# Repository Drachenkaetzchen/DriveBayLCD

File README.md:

This is a controller board for the DOGM LCD which can be controlled via USB. It is designed to fit into the 5 1/4" drive bay of your computer. It supports 6 LEDs and 6 Switches/Buttons.

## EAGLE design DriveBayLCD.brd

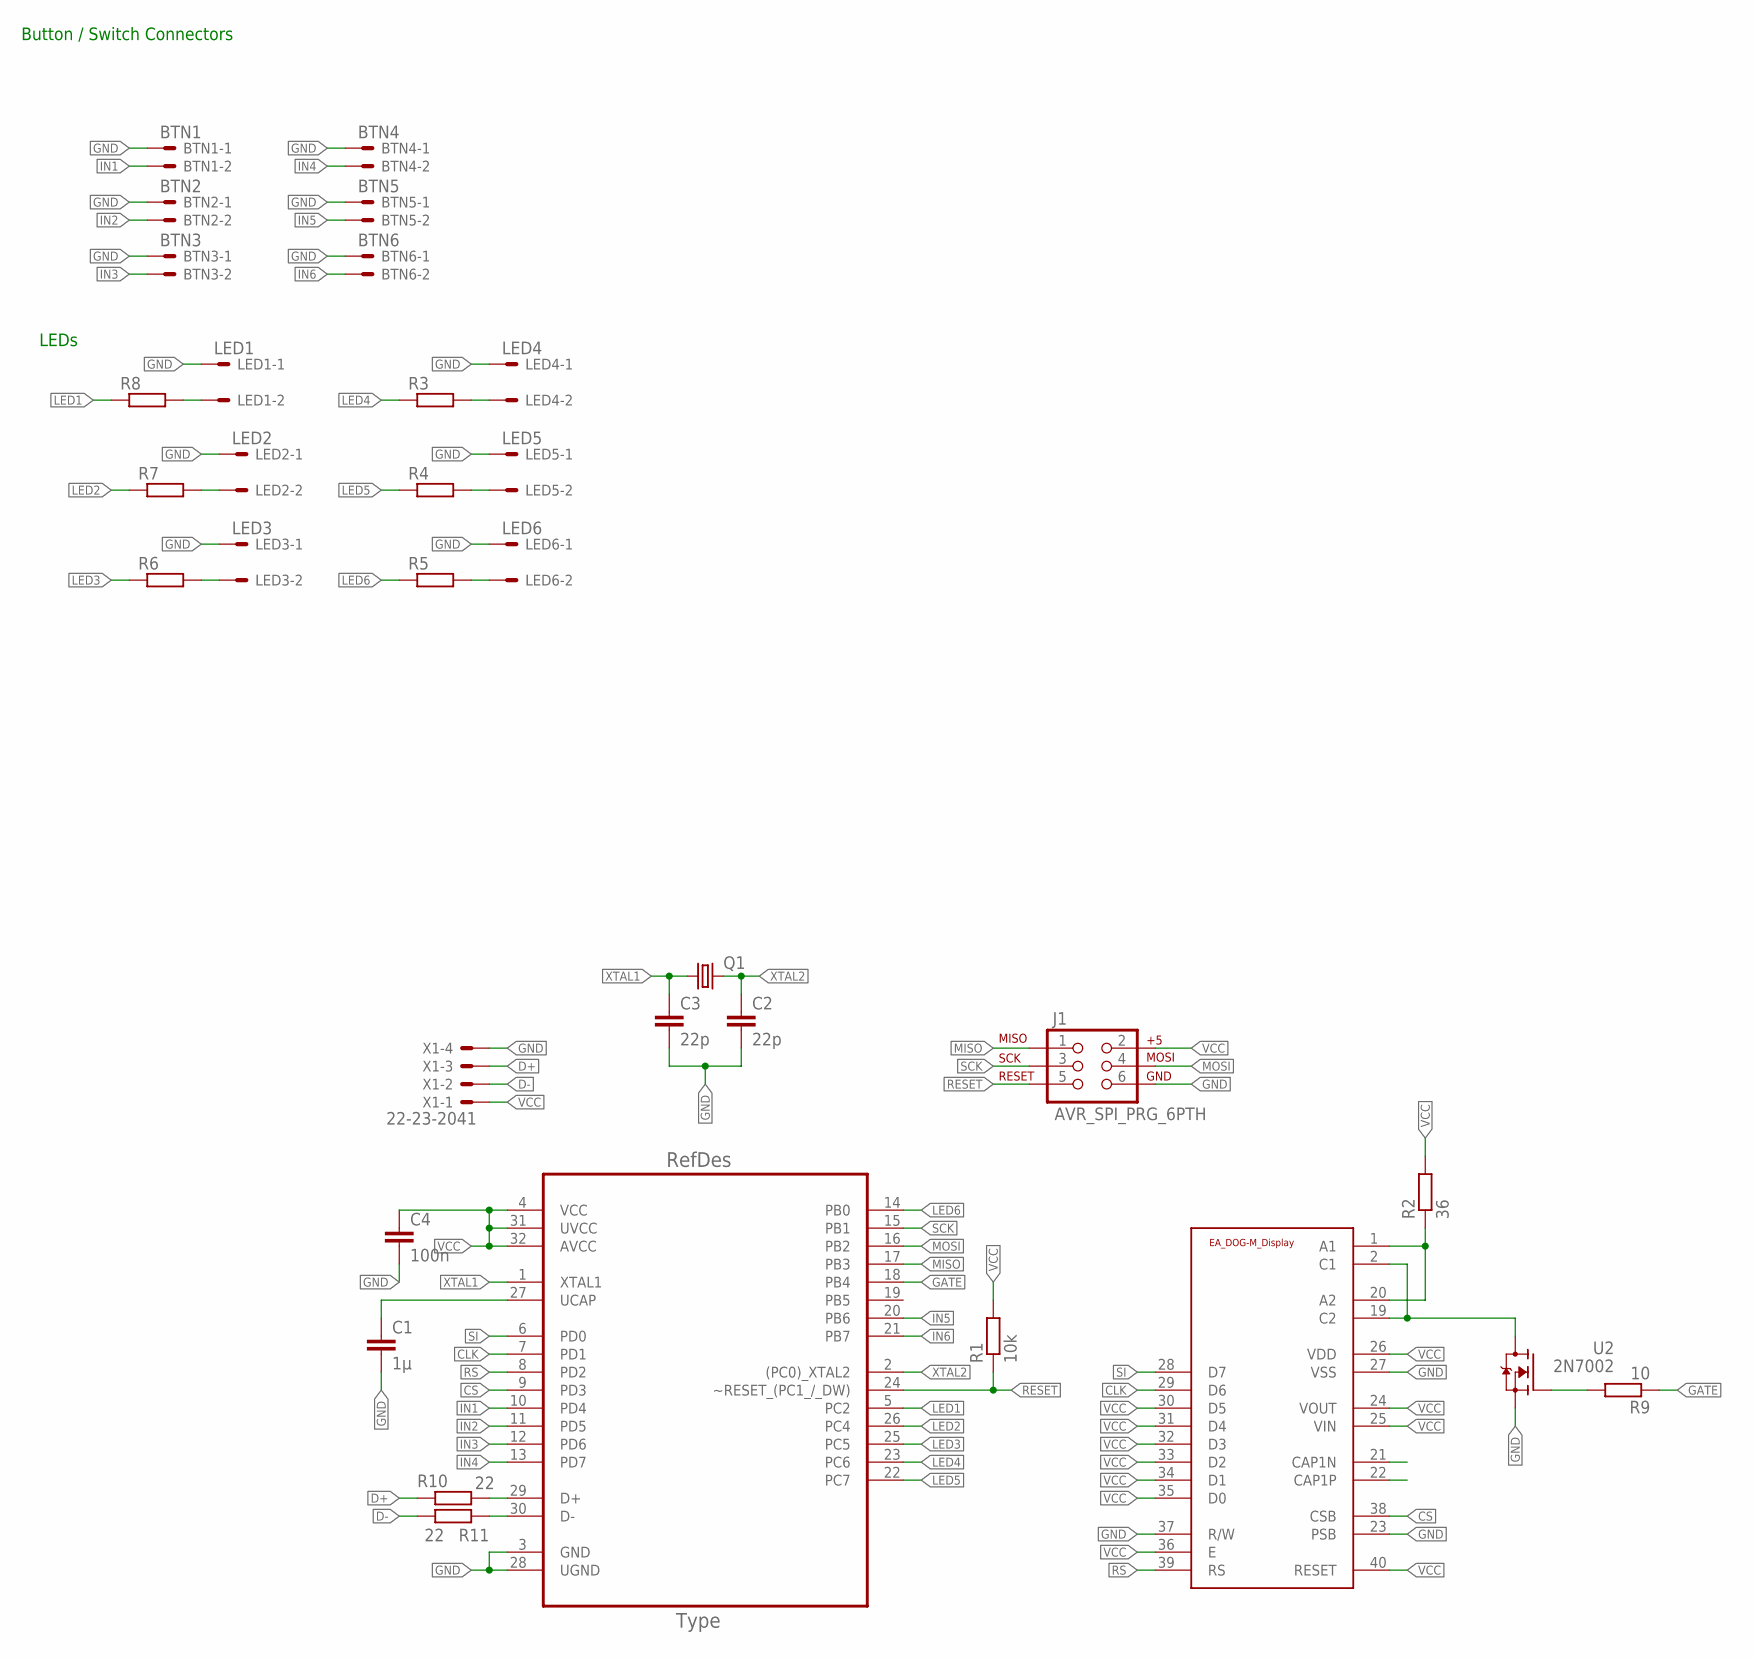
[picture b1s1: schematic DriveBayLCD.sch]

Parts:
BTN1: BTN1; 22-23-2021
BTN2: BTN2; 22-23-2021
BTN3: BTN3; 22-23-2021
BTN4: BTN4; 22-23-2021
BTN5: BTN5; 22-23-2021
BTN6: BTN6; 22-23-2021
C1: 1µ; C0805
C2, C3: 22p; C0805
C4: 100n; C0805
J1: AVR_SPI_PRG_6PTH; 2X3
LED1: LED1; 22-23-2021
LED2: LED2; 22-23-2021
LED3: LED3; 22-23-2021
LED4: LED4; 22-23-2021
LED5: LED5; 22-23-2021
LED6: LED6; 22-23-2021
Q1: CRYSTALHC49S; HC49/S
R1: 10k; R0805
R2: 36; R0805
R3, R4, R5, R6, R7, R8: R-EU_R0805; R0805
R9: 10; R0805
R10, R11: 22; R0805
U1: ATMEGA32U2-AU; QFP80P900X900X120-32N
U2: 2N7002; SOT23-3-ROTATED
U$1: EA_DOG-M_DISPLAY; E_DOG-M_DISPLAY
X1: 22-23-2041

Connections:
CLK: U1.7 (PD1), U$1.29 (D6)
CS: U1.9 (PD3), U$1.38 (CSB)
D+: R10.2, X1.3
D-: R11.2, X1.2
GATE: R9.1, U1.18 (PB4)
GND: BTN1.1, BTN2.1, BTN3.1, BTN4.1, BTN5.1, BTN6.1, C1.2, C2.2, C3.2, C4.2, J1.6, LED1.1, LED2.1, LED3.1, LED4.1, LED5.1, LED6.1, U1.3 (GND), U1.28 (UGND), U2.2 (S), U$1.23 (PSB), U$1.27 (VSS), U$1.37 (R/W), X1.4
IN1: BTN1.2, U1.10 (PD4)
IN2: BTN2.2, U1.11 (PD5)
IN3: BTN3.2, U1.12 (PD6)
IN4: BTN4.2, U1.13 (PD7)
IN5: BTN5.2, U1.20 (PB6)
IN6: BTN6.2, U1.21 (PB7)
LED1: R8.1, U1.5 (PC2)
LED2: R7.1, U1.26 (PC4)
LED3: R6.1, U1.25 (PC5)
LED4: R3.1, U1.23 (PC6)
LED5: R4.1, U1.22 (PC7)
LED6: R5.1, U1.14 (PB0)
MISO: J1.1, U1.17 (PB3)
MOSI: J1.4, U1.16 (PB2)
unnamed: LED1.2, R8.2
unnamed: LED2.2, R7.2
unnamed: LED3.2, R6.2
unnamed: LED6.2, R5.2
unnamed: C1.1, U1.27 (UCAP)
unnamed: LED5.2, R4.2
unnamed: LED4.2, R3.2
unnamed: R2.1, U$1.1 (A1), U$1.20 (A2)
unnamed: R9.2, U2.1 (G)
unnamed: R10.1, U1.29 (D+)
unnamed: R11.1, U1.30 (D-)
RESET: J1.5, R1.1, U1.24 (~RESET_(PC1_/_DW))
RS: U1.8 (PD2), U$1.39 (RS)
SCK: J1.3, U1.15 (PB1)
SI: U1.6 (PD0), U$1.28 (D7)
V$1: U2.3 (D), U$1.2 (C1), U$1.19 (C2)
VCC: C4.1, J1.2, R1.2, R2.2, U1.4 (VCC), U1.31 (UVCC), U1.32 (AVCC), U$1.24 (VOUT), U$1.25 (VIN), U$1.26 (VDD), U$1.30 (D5), U$1.31 (D4), U$1.32 (D3), U$1.33 (D2), U$1.34 (D1), U$1.35 (D0), U$1.36 (E), U$1.40 (RESET), X1.1
XTAL1: C3.1, Q1.1, U1.1 (XTAL1)
XTAL2: C2.1, Q1.2, U1.2 ((PC0)_XTAL2)

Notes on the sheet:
Button / Switch Connectors
LEDs

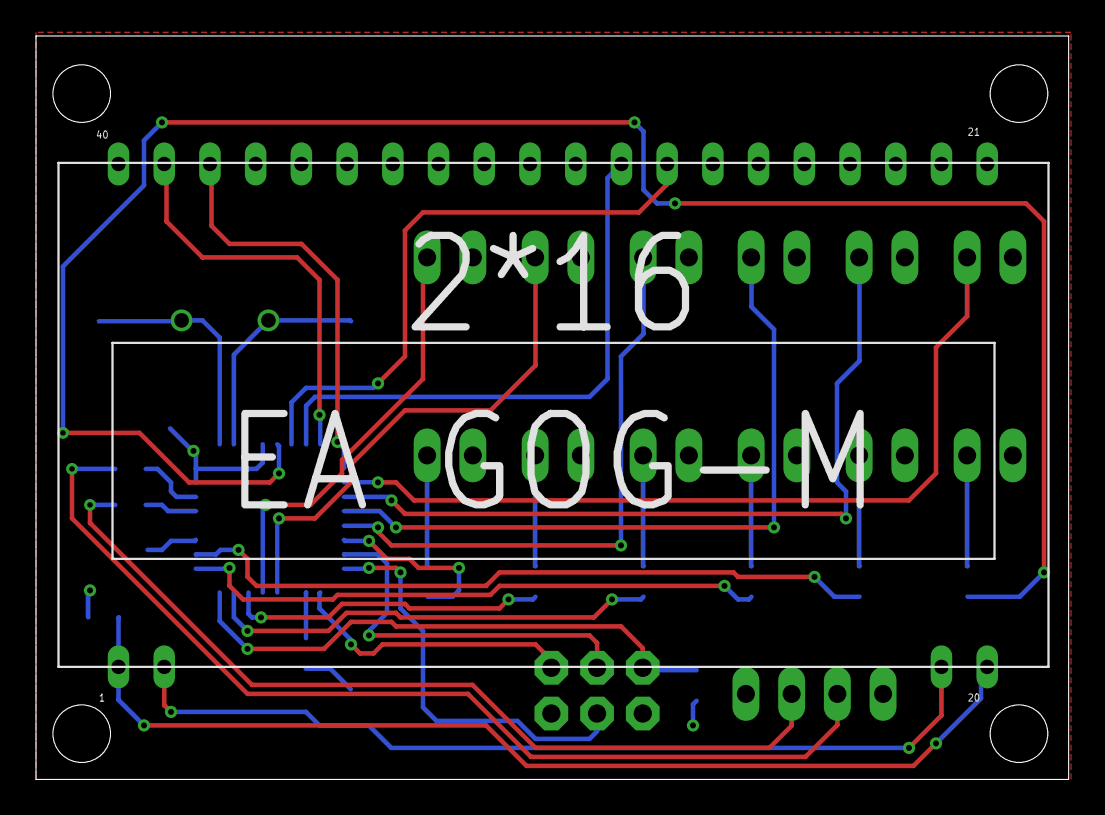
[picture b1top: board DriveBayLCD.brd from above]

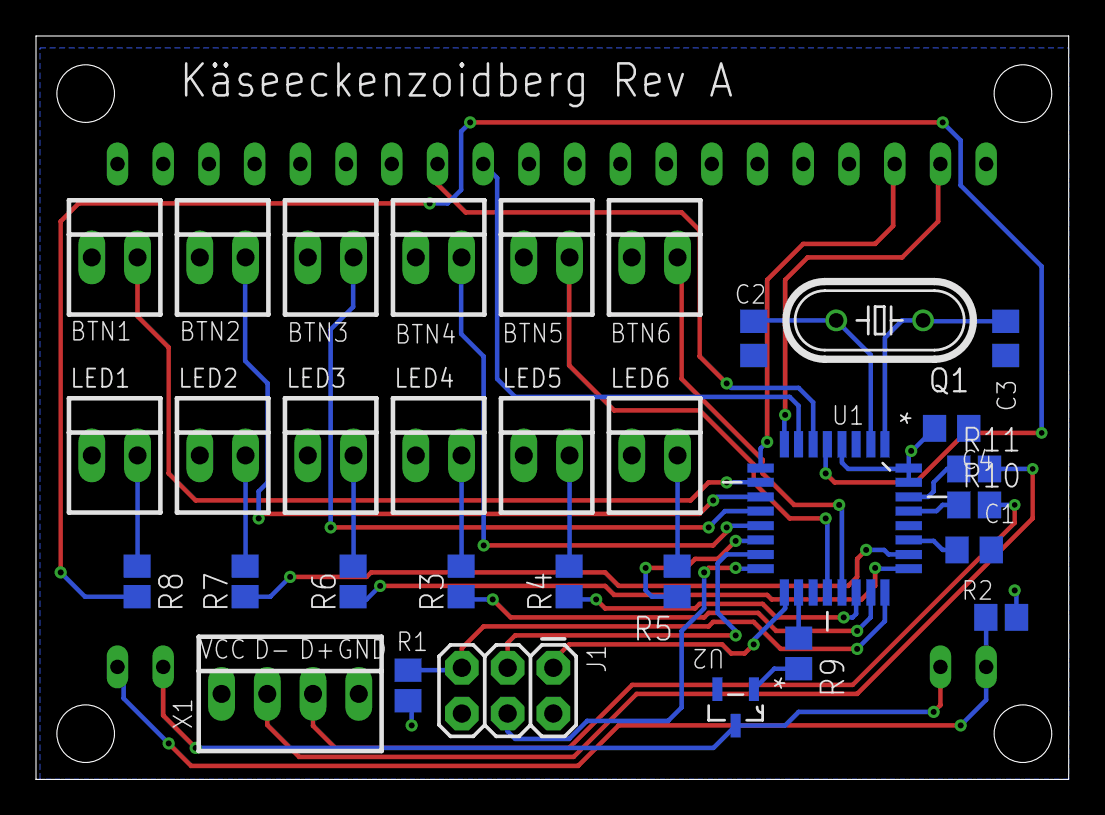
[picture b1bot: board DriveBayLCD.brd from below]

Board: 2 copper layers, 57.4 x 41.3 mm, 33 parts (32 on the bottom side), 39 nets.

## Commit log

2014-06-28 Added casing for 6x RAFI 107.104 buttons and 6x SMU1069 3mm LED casings
2014-07-25 Added mising 22 ohms line resistors

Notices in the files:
parts and their libraries:
SparkFun: Licensing: CC v3.0 Share-Alike You are welcome to use this library for commercial purposes.
